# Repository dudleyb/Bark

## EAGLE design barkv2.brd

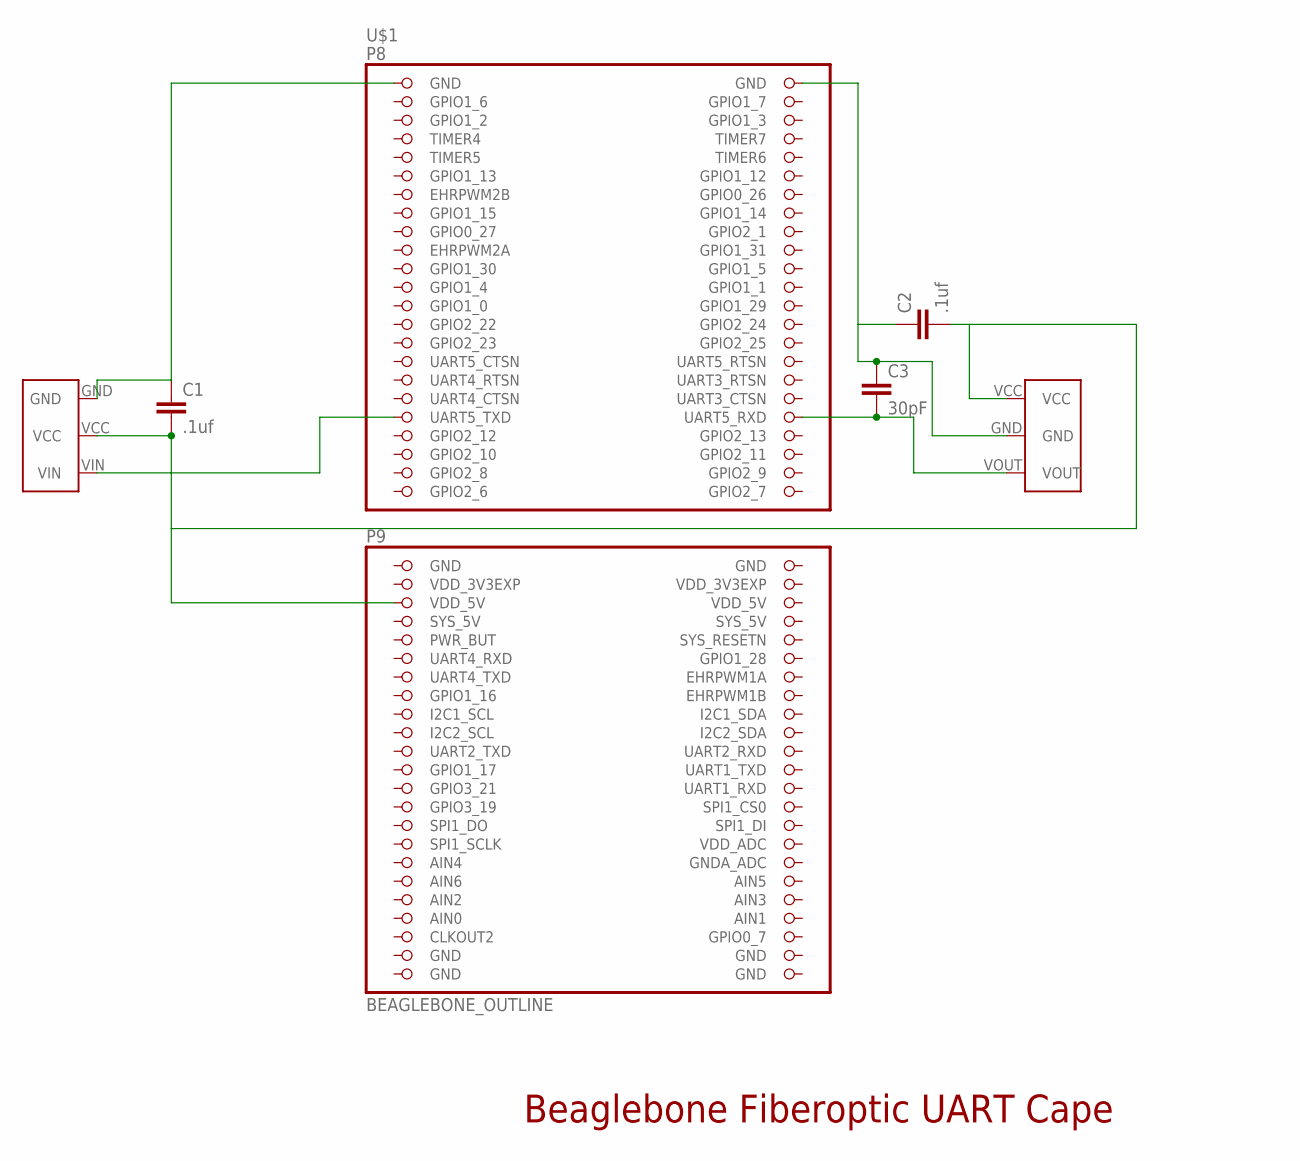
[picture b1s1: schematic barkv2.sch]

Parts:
C1, C2: .1uf; 0805
C3: 30pF; 0805
U$1: BEAGLEBONE_OUTLINE; BEAGLEBONE_SHIELD
U$2: DLT1160; DLT
U$3: DLR1160; DLR

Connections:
AIN0: U$1.85 (AIN0)
GND: U$1.47 (GND), U$1.48 (GND), U$1.89 (GND), U$1.90 (GND), U$1.91 (GND), U$1.92 (GND)
unnamed: U$1.37 (UART5_TXD), U$2.VIN
unnamed: C3.2, U$1.38 (UART5_RXD), U$3.VOUT
unnamed: C2.1, C3.1, U$1.2 (GND), U$3.GND
unnamed: C1.1, U$1.1 (GND), U$2.GND
unnamed: C1.2, C2.2, U$1.51 (VDD_5V), U$2.VCC, U$3.VCC
SYS_5V: U$1.53 (SYS_5V)
VDD_3V3EXP: U$1.49 (VDD_3V3EXP), U$1.50 (VDD_3V3EXP)
VDD_5V: U$1.52 (VDD_5V)

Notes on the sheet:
Beaglebone Fiberoptic UART Cape

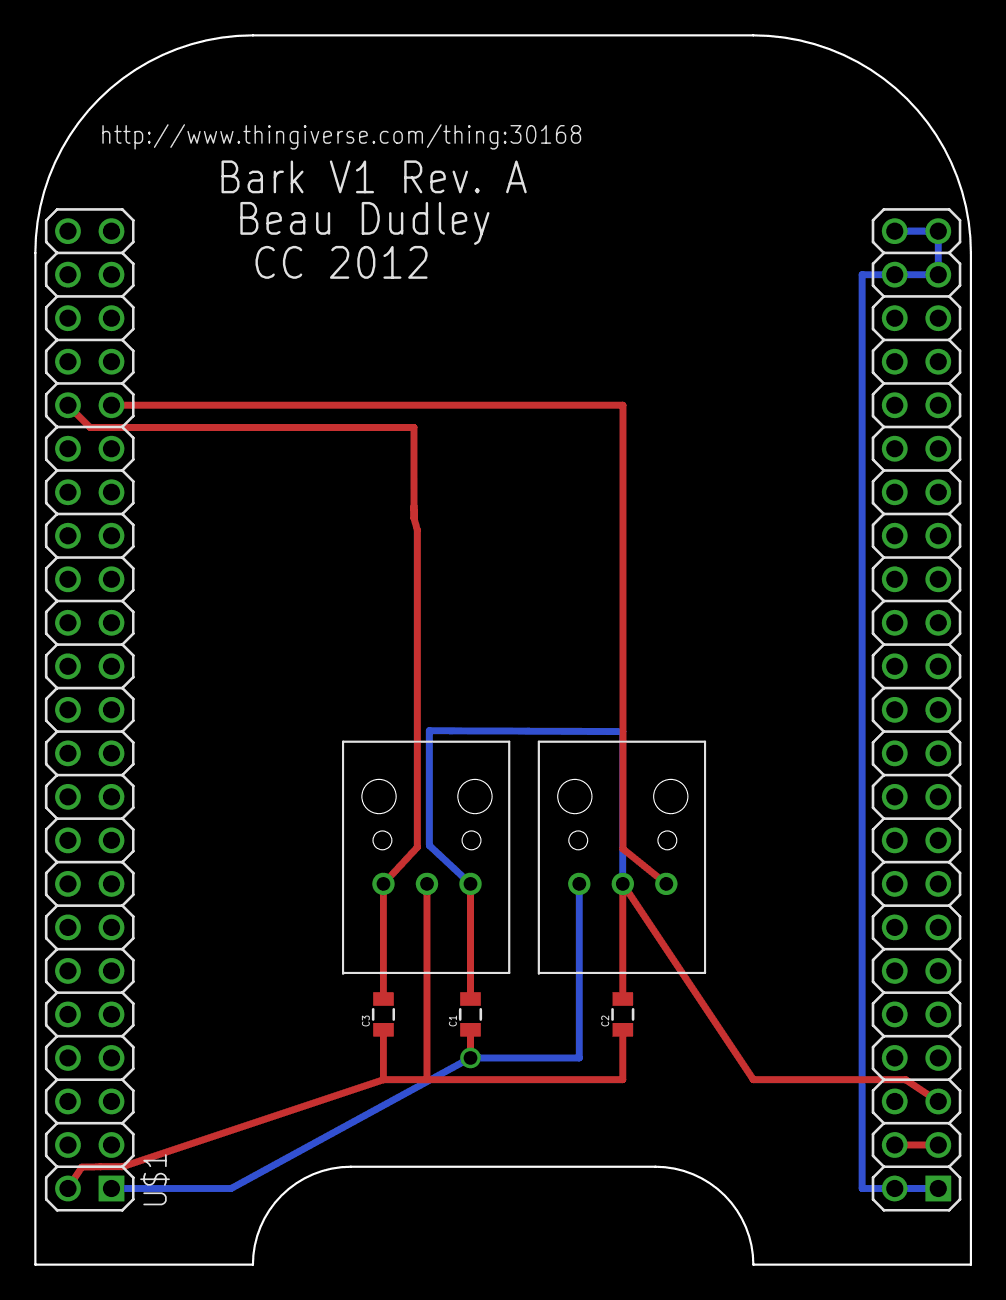
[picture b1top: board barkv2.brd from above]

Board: 2 copper layers, 54.6 x 71.8 mm, 6 parts (0 on the bottom side), 7 nets.

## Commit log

2012-09-20 Beaglebone Bark Cape

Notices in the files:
parts and their libraries:
SparkFun-Passives: Licensing: CC v3.0 Share-Alike You are welcome to use this library for commercial purposes.
